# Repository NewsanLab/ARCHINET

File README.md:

# ARCHINET
Archi Net es una placa de desarrollo diseñada para facilitar la conectividad mediante WiFi, Ethernet y Bluetooth Low Energy (BLE). Cuenta con 4 entradas analógicas y 8 entradas/salidas digitales.

El diseño está pensado para que todas las funciones puedan ser programadas y controladas directamente desde el microcontrolador ARCHI (basado en RP2040), sin necesidad de programar el ESP32 por separado. Este actúa como un coprocesador de comunicaciones, operando mediante comandos enviados en formato Json.

## Especificaciones

* **Voltaje de Entrada del Shield:** 5V a 12V.
* **Conectividad Wi-Fi:** Estándar 802.11 b/g/n (2.4 GHz) con soporte para modos de estación, Punto de Acceso (AP) y Wi-Fi Direct (ESP32-S3).
* **Conectividad Bluetooth:** Bluetooth LE 5.0 (Bluetooth Low Energy).
* **Conectividad Ethernet:** Compatible con 10Base-T/100Base-TX Ethernet (WIZnet W5500).
* **Voltaje de Operación Interno:** Los módulos internos (ESP32-S3 y W5500) operan típicamente a 3.3V, provistos por reguladores a bordo del shield.
* **Pines de Entrada/Salida (I/O):**
    * 4 Entradas/Salidas Analógicas.
    * 8 Entradas/Salidas Digitales.
* **Programación/Depuración:** Incluye un puerto USB JTAG integrado para la programación y depuración directa del ESP32-S3.

## Diagrama en Bloques 

#### El shield ArchiNET se divide en 4 bloques funcionales principales:

* **Fuente de Alimentación:** Este bloque garantiza la alimentación estable a los bloques de conectividad.
* **Archi:** Es el microcontrolador principal que controla la comunicación y funcionalidad de los bloques de conectividad (ESP32 y Ethernet WIZNET W5500).
* **ESP32-S3:** Funciona como un coprocesador dedicado a la conectividad inalámbrica, comunicándose con Archi mediante interfaces como UART o SPI.
* **Ethernet (WIZNET W5500):** Proporciona la conexión de red cableada a través de un puerto RJ45, permitiendo una comunicación Ethernet.

## Fuente de alimentación
El siguiente diagrama en bloque muestra la distribución de voltaje.

El shield ArchiNet tiene una entrada para una fuente externa de +5V con una capacidad de hasta 2A.

Este voltaje de +5V se utiliza para la alimentación principal de la placa. La placa ArchiNet, a su vez, regula este voltaje para obtener una salida de +3.3V.

Esta salida de +3.3V es la que se utiliza para alimentar los módulos de bajo voltaje, como el Wiznet 5500 , el ESP32S3 y sensores

# 💻 Software

## Conexión a Ethernet

Para realizar una conexión por medio de Ethernet se deben tener cargadas las siguientes librerías en la carpeta `CIRCUITPY/lib`:

- `Adafruit_Bus_Device`
- `Adafruit_Wiznet5K`
- `Adafruit_Connection_Manager`
- `Adafruit_Requests`
- `Adafruit_Ticks`

### ⚙️ Configuración de pines

- **SPI**:
  - `SCK` → `GP10`
  - `MOSI` → `GP11`
  - `MISO` → `GP12`
  - `Chip Select (CS)` → `GP9`

###  Prueba de conexión inicial con ETHERNET

Este script permite comprobar que el dispositivo se conecta correctamente a la red mediante Ethernet.

### ¿Qué hace el script?

1. Configura el bus SPI y el pin CS.
2. Inicializa el módulo Ethernet `WIZNET5K`.
3. Crea una sesión HTTP con `adafruit_requests`.
4. Muestra:
   - Versión del chip
   - Dirección MAC
   - Dirección IP asignada

## Ejemplo: Consulta de IP por Ethernet

<a href="https://github.com/NewsanLab/ARCHINET/blob/main/Software/Example/Ethernet/Ejemplo%201%20Consulta%20IP/01.py" target="_blank" style="text-decoration:none; padding:6px 12px; background-color:#0366d6; color:white; border-radius:6px; font-weight:bold;"> Ver código completo en GitHub</a>

###  Fragmento del código 
```python
import board
import busio
import digitalio
import adafruit_connection_manager
import adafruit_requests
from adafruit_wiznet5k.adafruit_wiznet5k import WIZNET5K

spi = busio.SPI(board.GP10, MOSI=board.GP11, MISO=board.GP12)
cs = digitalio.DigitalInOut(board.GP9)
eth = WIZNET5K(spi, cs)

pool = adafruit_connection_manager.get_radio_socketpool(eth)
ssl_context = adafruit_connection_manager.get_radio_ssl_context(eth)
requests = adafruit_requests.Session(pool, ssl_context)

print("Chip Version:", eth.chip)
print("MAC Address:", [hex(i) for i in eth.mac_address])
print("My IP address is:", eth.pretty_ip(eth.ip_address))

```
## ESP32 como Coprocesador (modo UART)

El ESP32 se utiliza como coprocesador encargado de gestionar la conexión WiFi. La comunicación entre el microcontrolador principal (ej. RP2040, Archi u otros) y el ESP32 se realiza mediante UART o SPI, mediante el envío de **comandos en formato JSON**.

---

###  Modos de operación

- **UART**: Se comunica a través de pines TX/RX, usando comandos y respuestas JSON.
- **SPI**: Alternativamente, se puede implementar una versión basada en SPI (no cubierta en este ejemplo, pero compatible).

---

## Conexión WiFi / BLE vía UART

Este ejemplo muestra cómo controlar el ESP32 como coprocesador para conectarse a una red WiFi/BLE mediante UART.

### Conceptos clave

- Comunicación UART entre el microcontrolador principal y el ESP32.
- El pin `ready` indica cuándo el ESP32 está disponible para recibir comandos.
- Uso de JSON para enviar comandos como `CONNECT`, `SCAN`, `STATUS`, etc.
- Reset físico al ESP32 para asegurar un arranque limpio.

---

### ⚙️ Configuración de pines
- **UART y pines de control**:

  - `UART TX` → `GP12`
  - `UART RX` → `GP13`
  - `Pin ready` → `GP14`
  - `Pin reset` → `GP15`

---

### ¿Qué hace el script?

1. Reinicia el ESP32 con un pulso en el pin `reset`.
2. Espera la señal `ready` del ESP32.
3. Envía el comando `CONNECT` con SSID y contraseña.
4. Recibe las respuestas en formato JSON.
5. Finaliza cuando se recibe `{"end": true}` desde el ESP32.

---

###  Ejemplo: Primera conexión a la red

<a href="https://github.com/NewsanLab/ARCHINET/blob/main/Software/Example/WiFi/Conectar%20a%20WiFi/code.py" target="_blank" style="text-decoration:none; padding:6px 12px; background-color:#0366d6; color:white; border-radius:6px; font-weight:bold;"> Ver código completo en GitHub</a>

### Fragmento del código

```python
esp = ESP32UART(tx_pin=board.GP12, rx_pin=board.GP13, ready_pin=board.GP14)

if esp.esperar_ready(timeout=10):
    esp.solicitar_comando({"cmd": "CONNECT", "ssid": "tu_ssid", "pass": "tu_password"})
    esp.leer_respuesta(timeout=20)
else:
    print("ESP32 no está listo.")

```
---
### Ejemplo: Primera conexión mediante BLE 

Para iniciar comunicación BLE se realiza mediante la misma manera por comandos:

```python
 #Inicia BLE->Con el siguiente comando por defecto tiene el nombre de ARCHINET_BLEXX  
    print("\n--- TEST: CONNECT BLE---")
    esp.solicitar_comando({"cmd": "BLEINIT"})
    esp.leer_respuesta(timeout=20) #respuesta el nombre del dispositivo

    while True:
        esp.solicitar_comando({"cmd": "BLETX","data": "{pcb:archinet, version:v2}"})#tx
        esp.solicitar_comando({"cmd": "BLERX"})
        esp.leer_respuesta(timeout=15) #respuesta del ble rx
        time.sleep(2) 
```
Una vez que tienes la conexión hecha, puedes realizar  una app escritorio/celular para obtener datos. 

### Ejemplo de APP recepción y transmisión 

---

### 📋 Lista de comandos

| Comando       | Parámetros                      | Descripción                                                                 | 📄 Código de ejemplo                                                                 |
|---------------|----------------------------------|-----------------------------------------------------------------------------|--------------------------------------------------------------------------------------|
| `SCAN`        | *(ninguno)*                     | Escanea y lista redes WiFi disponibles.                                    | [🔗 Ver ejemplo](https://github.com/NewsanLab/ARCHINET/blob/main/Software/Example/WiFi/Escanear/code.py)          |
| `CONNECT`     | `ssid`, `pass`                  | Conecta a una red WiFi específica.                                         | [🔗 Ver ejemplo](https://github.com/NewsanLab/ARCHINET/blob/main/Software/Example/WiFi/Conectar%20a%20WiFi/code.py)       |
| `DISCONNECT`  | `target` (`"WiFi"` o `"AP"`)    | Desconecta de la red o cierra el punto de acceso.                          | [🔗 Ver ejemplo](https://github.com/NewsanLab/ARCHINET/blob/main/Software/Example/WiFi/Desconectar%20Red/code.py)    |
| `AP`          | `ssid`, `pass`                  | Crea un punto de acceso (Access Point).                                    | [🔗 Ver ejemplo](https://github.com/NewsanLab/ARCHINET/blob/main/Software/Example/WiFi/Conectar%20a%20AP/code.py)            |
| `PING`        | *(ninguno)*                     | Verifica si el ESP32 está activo y responde con su IP.                     | [🔗 Ver ejemplo](https://github.com/NewsanLab/ARCHINET/blob/main/Software/Example/WiFi/Informaci%C3%B3n%20de%20conexi%C3%B3n/code.py)          |
| `INFO`        | *(ninguno)*                     | Devuelve información del sistema: IP, RSSI y memoria disponible.           | [🔗 Ver ejemplo](https://github.com/NewsanLab/ARCHINET/blob/main/Software/Example/WiFi/Informaci%C3%B3n%20de%20conexi%C3%B3n/code.py)          |
| `GET`         | `url`                           | Realiza una petición HTTP GET a la URL indicada.                           | [🔗 Ver ejemplo](https://github.com/NewsanLab/ARCHINET/blob/main/Software/Example/WiFi/Consulta%20GET/code.py)           |
| `POST`        | `url`, `data`                   | Envía datos mediante HTTP POST (JSON) a la URL especificada.               | [🔗 Ver ejemplo](https://github.com/NewsanLab/ARCHINET/blob/main/Software/Example/WiFi/Consulta%20POST/code.py)          |
| `WebServer`   | `label`, `data`                 | Crea o actualiza un endpoint en el servidor embebido del ESP32.            | [🔗 Ver ejemplo](https://github.com/NewsanLab/ARCHINET/blob/main/Software/Example/WiFi/WebServer-API-WiFi/code.py)     |
| `HTML`        | `html`                          | Inyecta HTML personalizado en el servidor web embebido.                    | [🔗 Ver ejemplo](https://github.com/NewsanLab/ARCHINET/blob/main/Software/Example/WiFi/A%C3%B1adir%20HTML/codehtml.py)          |
| `UART_OFF`    | `UART_OFF`                      | Apaga el UART para utilizar el Ethernet, para volver utilzar reiniciar esp32.| [🔗 Ver ejemplo](https://github.com/NewsanLab/ARCHINET/blob/main/Software/Example/UART_OFF%26ETHERNET/Code.py) |
| `BLEINIT`    | *(ninguno o name)*                    | Inicia BLE por defecto crea el nombre del dispositivo | [🔗 Ver ejemplo](https://github.com/NewsanLab/ARCHINET/blob/main/Software/Example/BLE/code.py)|
| `BLETX`    |  `data`                   | Realiza la transmisión de datos de BLE , se debe mandar los datos en el parametro data en formato json | [🔗 Ver ejemplo](https://github.com/NewsanLab/ARCHINET/blob/main/Software/Example/BLE/code.py)|
| `BLERX`    |  *(ninguno)*                  | Realiza la recepción de datos de BLE  | [🔗 Ver ejemplo](https://github.com/NewsanLab/ARCHINET/blob/main/Software/Example/BLE/code.py)|
| `BLEOFF`    | *(ninguno o name)*                    | Desactiva el BLE | [🔗 Ver ejemplo](https://github.com/NewsanLab/ARCHINET/blob/main/Software/Example/BLE/BLEOFF.py)|

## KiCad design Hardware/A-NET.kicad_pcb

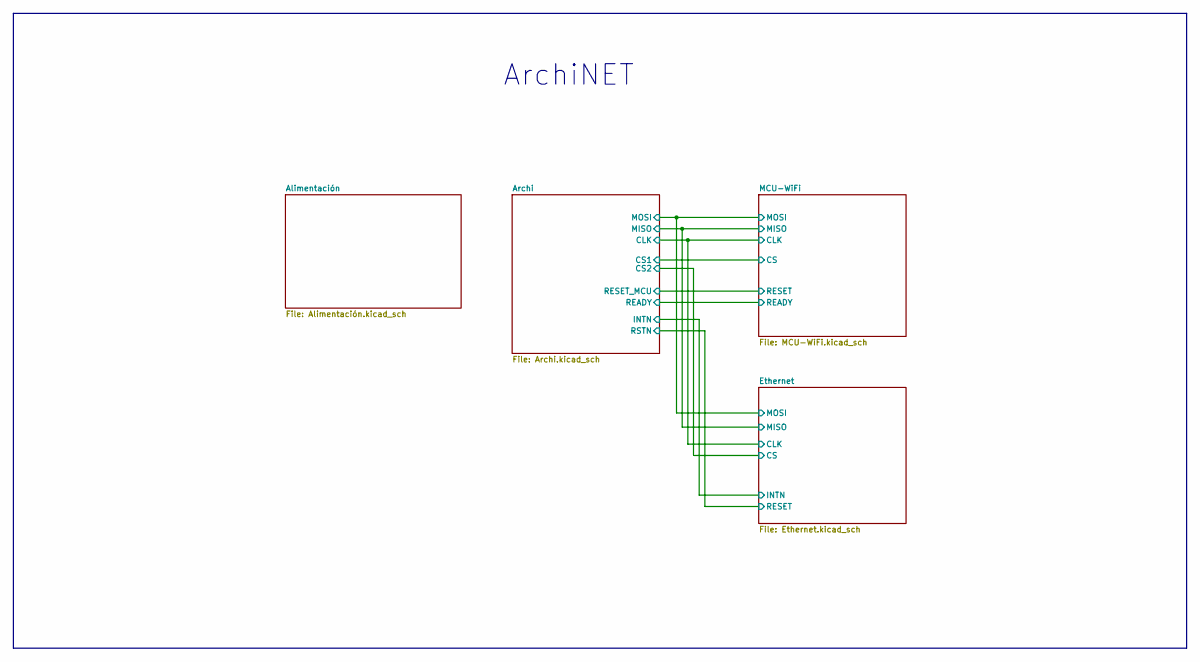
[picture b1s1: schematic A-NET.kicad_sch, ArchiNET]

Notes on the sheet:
ArchiNET

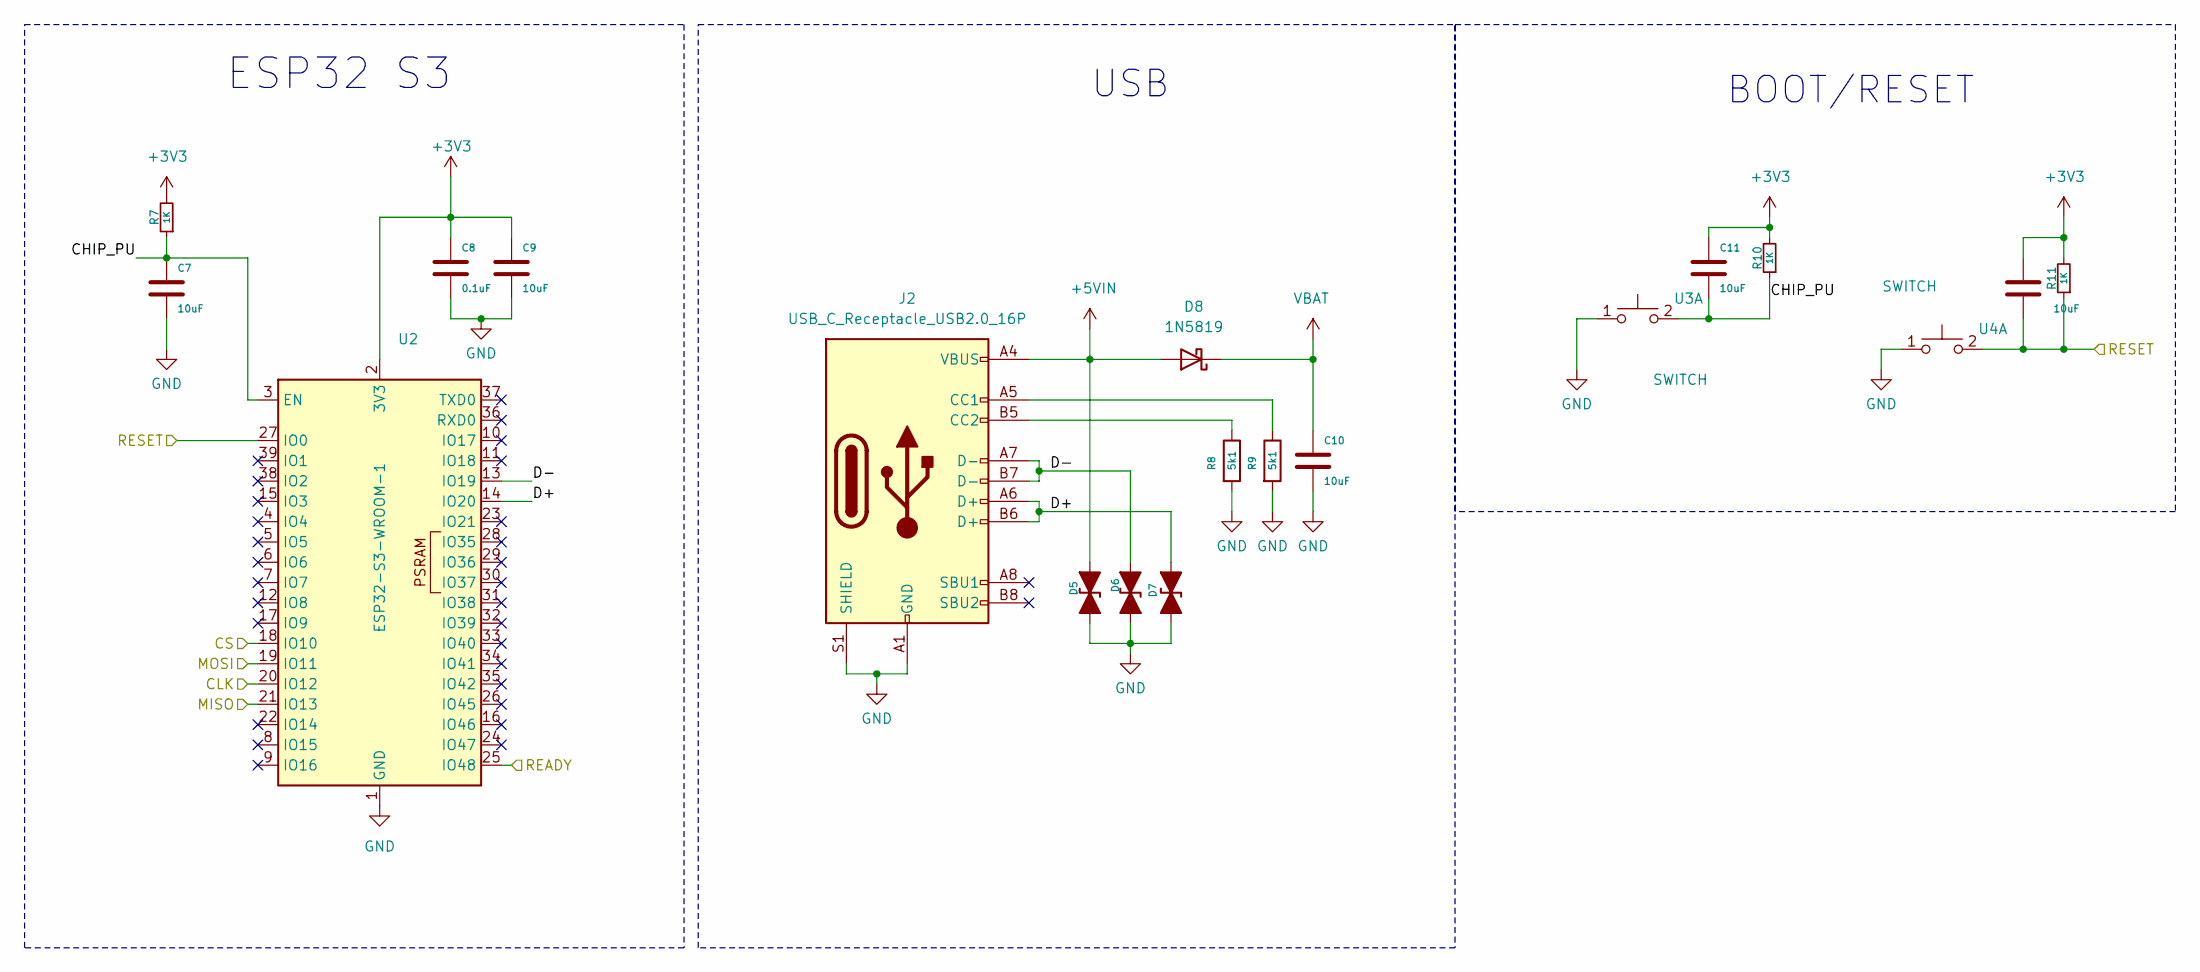
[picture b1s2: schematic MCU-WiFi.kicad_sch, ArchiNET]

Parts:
C7, C9, C10, C11, C12: 10uF; C_0603_1608Metric; PartNumber CL10X106MO8NRNC
C8: 0.1uF; C_0603_1608Metric; PartNumber CC0603KRX7R7BB104
D5, D6, D7: D_TVS_Filled; D_0402_1005Metric; PartNumber ESD9B5.0ST5G
D8: 1N5819; Nexperia_CFP3_SOD-123W; PartNumber 1N5819WS
J2: USB_C_Receptacle_USB2.0_16P; USB_C_Receptacle_HRO_TYPE-C-31-M-12; PartNumber USB4105-GF-A
R7, R10, R11: 1K; R_0603_1608Metric_Pad0.98x0.95mm_HandSolder; PartNumber RCS06031K00FKEA
R8, R9: 5k1; R_0402_1005Metric; PartNumber ERJ-PA2F5101X
U2: ESP32-S3-WROOM-1; PartNumber ESP32-S3-WROOM-1-N8
U3, U4: SWITCH; SW_Push_1P1T_XKB_TS-1187A; PartNumber PTS526SK15SMTR2 LFS

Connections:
+3V3: C8.1, C9.1, C11.1, C12.1, R7.2, R10.2, R11.2, U2.2 (3V3); also elsewhere on the board
+5VIN: D5.2 (A2), D8.2 (A), J2.A4 (VBUS), J2.A9 (VBUS), J2.B4 (VBUS), J2.B9 (VBUS); also elsewhere on the board
/Archi/CLK: U2.20 (IO12); also elsewhere on the board
/Archi/CS1: U2.18 (IO10); also elsewhere on the board
/Archi/MISO: U2.21 (IO13); also elsewhere on the board
/Archi/MOSI: U2.19 (IO11); also elsewhere on the board
/Archi/READY: U2.25 (IO48); also elsewhere on the board
/Archi/RESET_MCU: C12.2, R11.1, U2.27 (IO0), U4.2 (D); also elsewhere on the board
/MCU-WiFi/CHIP_PU: C7.1, C11.2, R7.1, R10.1, U2.3 (EN), U3.2 (D)
/MCU-WiFi/D+: D7.2 (A2), J2.A6 (D+), J2.B6 (D+), U2.14 (IO20)
/MCU-WiFi/D-: D6.2 (A2), J2.A7 (D-), J2.B7 (D-), U2.13 (IO19)
GND: C7.2, C8.2, C9.2, C10.2, D5.1 (A1), D6.1 (A1), D7.1 (A1), J2.A1 (GND), J2.A12 (GND), J2.B1 (GND), J2.B12 (GND), J2.S1 (SHIELD), R8.2, R9.2, U2.1 (GND), U2.40 (GND), U2.41 (GND), U3.1 (C), U4.1 (C); also elsewhere on the board
unnamed: J2.A5 (CC1), R9.1
unnamed: J2.B5 (CC2), R8.1
VBAT: C10.1, D8.1 (K); also elsewhere on the board

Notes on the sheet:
USB
BOOT/RESET
ESP32 S3

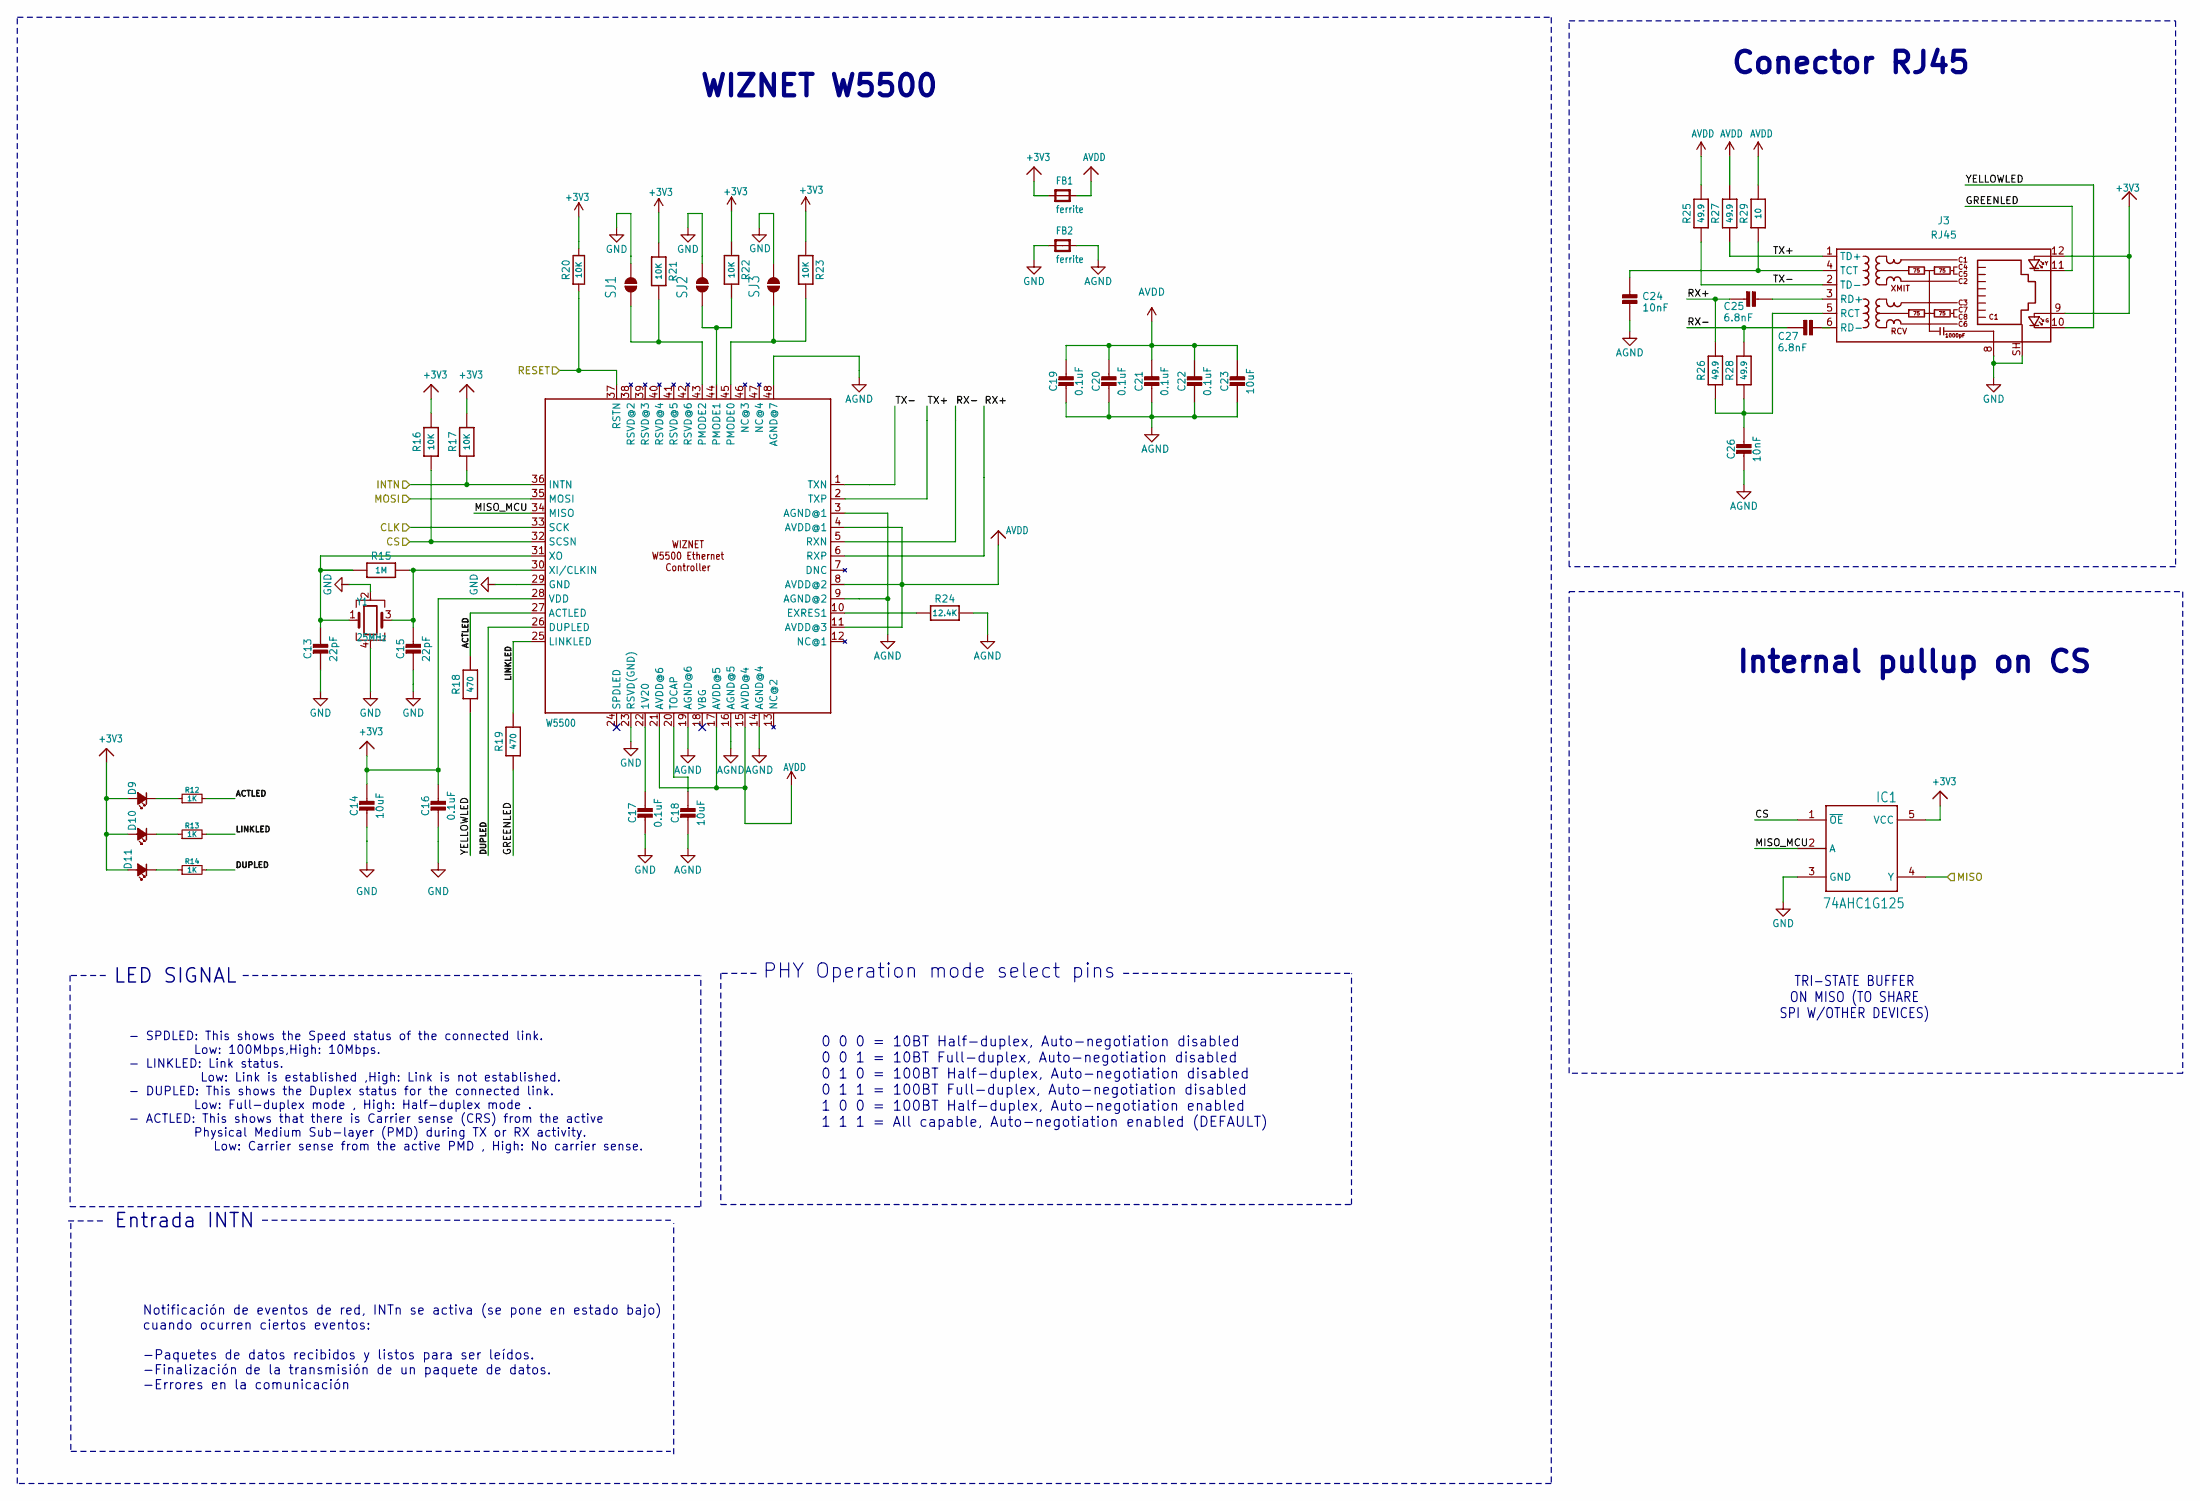
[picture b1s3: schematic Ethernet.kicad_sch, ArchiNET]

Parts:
C13, C15: 22pF; C_0603_1608Metric; PartNumber C0603C220K4GACTU
C14, C18, C23: 10uF; C_0603_1608Metric; PartNumber CL10X106MO8NRNC
C16, C17, C19, C20, C21, C22: 0.1uF; C_0603_1608Metric; PartNumber CC0603KRX7R7BB104
C24, C26: 10nF; C_0603_1608Metric; PartNumber C0603C103K4RECTU
C25, C27: 6.8nF; C_0603_1608Metric; PartNumber KGM15AR71C682KT
D9, D10, D11: LED_POW; LED_0603_1608Metric_Pad1.05x0.95mm_HandSolder; PartNumber B1931NG--20D001114U1930
FB1: ferrite; L_0603_1608Metric; PartNumber MH1608-121Y
FB2: ferrite; R_0603_1608Metric; PartNumber MH1608-121Y
IC1: 74AHC1G125; SOT-353_SC-70-5; PartNumber SN74AHC1G125DCKR
J3: RJ45; CONN12_ARJM11B1-009-AB-EW2_ABR; PartNumber ARJM11B1-009-AB-EW2
R12, R13, R14: 1K; R_0603_1608Metric_Pad0.98x0.95mm_HandSolder; PartNumber RCS06031K00FKEA
R15: 1M; R_0603_1608Metric; PartNumber RCS06031M00FKEA
R16, R17, R20, R21, R22, R23: 10K; R_0603_1608Metric; PartNumber RCS060310K0JNEA
R18, R19: 470; R_0603_1608Metric; PartNumber CRGP0603F470R
R24: 12.4K; R_0603_1608Metric; PartNumber RCS060312K4FKEA
R25, R26, R27, R28: 49.9; R_0603_1608Metric; PartNumber RCS060349R9FKEA
R29: 10; R_0603_1608Metric; PartNumber RCS060310R0FKEA
SJ1, SJ2, SJ3: SOLDERJUMPERREFLOW_NOPASTE; Jumper
U$1: W5500; PartNumber W5500
Y1: 25MHz; Crystal_SMD_TXC_7M-4Pin_3.2x2.5mm; PartNumber ABM3B-25.000MHZ-22-E-4-H-T

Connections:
+3V3: C14.1, C16.1, D9.2 (A), D10.2 (A), D11.2 (A), FB1.1, IC1.5 (VCC), J3.9, J3.12, R16.2, R17.2, R20.1, R21.1, R22.1, R23.1, U$1.28 (VDD); also elsewhere on the board
/Archi/CLK: U$1.33 (SCK); also elsewhere on the board
/Archi/INTN: R17.1, U$1.36 (INTN); also elsewhere on the board
/Archi/MISO: IC1.4 (Y); also elsewhere on the board
/Archi/MOSI: U$1.35 (MOSI); also elsewhere on the board
/Archi/RSTN: R20.2, U$1.37 (RSTN); also elsewhere on the board
/Ethernet/ACTLED: R12.2, R18.2, U$1.27 (ACTLED)
/Ethernet/CS: IC1.1 (~OE), R16.1, U$1.32 (SCSN); also elsewhere on the board
/Ethernet/DUPLED: R14.2, U$1.26 (DUPLED)
/Ethernet/GREENLED: J3.11, R19.1
/Ethernet/LINKLED: R13.2, R19.2, U$1.25 (LINKLED)
/Ethernet/MISO_MCU: IC1.2 (A), U$1.34 (MISO)
/Ethernet/RX+: C25.2, R26.2, U$1.6 (RXP)
/Ethernet/RX-: C27.2, R28.2, U$1.5 (RXN)
/Ethernet/TX+: J3.1 (TD+), R27.1, U$1.2 (TXP)
/Ethernet/TX-: J3.2 (TD-), R25.1, U$1.1 (TXN)
/Ethernet/YELLOWLED: J3.10, R18.1
AGND: C18.2, C19.2, C20.2, C21.2, C22.2, C23.2, C24.2, C26.2, FB2.2, R24.2, U$1.3 (AGND@1), U$1.9 (AGND@2), U$1.14 (AGND@4), U$1.16 (AGND@5), U$1.19 (AGND@6), U$1.48 (AGND@7)
AVDD: C19.1, C20.1, C21.1, C22.1, C23.1, FB1.2, R25.2, R27.2, R29.2, U$1.4 (AVDD@1), U$1.8 (AVDD@2), U$1.11 (AVDD@3), U$1.15 (AVDD@4), U$1.17 (AVDD@5), U$1.21 (AVDD@6)
GND: C13.2, C14.2, C15.2, C16.2, C17.2, FB2.1, IC1.3 (GND), J3.8, J3.SH, SJ1.2 (B), SJ2.2 (B), SJ3.2 (B), U$1.23 (RSVD(GND)), U$1.29 (GND), Y1.2, Y1.4; also elsewhere on the board
unnamed: D9.1 (K), R12.1
unnamed: D10.1 (K), R13.1
unnamed: D11.1 (K), R14.1
unnamed: C26.1, J3.5 (RCT), R26.1, R28.1
unnamed: C25.1, J3.3 (RD+)
unnamed: C27.1, J3.6 (RD-)
unnamed: C24.1, J3.4 (TCT), R29.1
unnamed: R21.2, SJ1.1 (A), U$1.43 (PMODE2)
unnamed: R22.2, SJ2.1 (A), U$1.44 (PMODE1)
unnamed: R23.2, SJ3.1 (A), U$1.45 (PMODE0)
unnamed: C17.1, U$1.22 (1V20)
unnamed: R24.1, U$1.10 (EXRES1)
unnamed: C18.1, U$1.20 (TOCAP)
unnamed: C15.1, R15.2, U$1.30 (XI/CLKIN), Y1.3
unnamed: C13.1, R15.1, U$1.31 (XO), Y1.1

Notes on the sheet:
PHY Operation mode select pins
Internal pullup on CS
Notificación de eventos de red, INTn se activa (se pone en estado bajo) cuando ocurren ciertos eventos: -Paquetes de datos recibidos y listos para ser leídos. -Finalización de la transmisión de un paquete de datos. -Errores en la comunicación
LED SIGNAL
TRI-STATE BUFFER ON MISO (TO SHARE SPI W/OTHER DEVICES)
0 0 0 = 10BT Half-duplex, Auto-negotiation disabled 0 0 1 = 10BT Full-duplex, Auto-negotiation disabled 0 1 0 = 100BT Half-duplex, Auto-negotiation disabled 0 1 1 = 100BT Full-duplex, Auto-negotiation disabled 1 0 0 = 100BT Half-duplex, Auto-negotiation enabled 1 1 1 = All capable, Auto-negotiation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
WIZNET W5500
- SPDLED: This shows the Speed status of the connected link. Low: 100Mbps,High: 10Mbps. - LINKLED: Link status. Low: Link is established ,High: Link is not established. - DUPLED: This shows the Duplex status for the connected link. Low: Full-duplex mode , High: Half-duplex mode . - ACTLED: This sho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
Entrada INTN
Conector RJ45

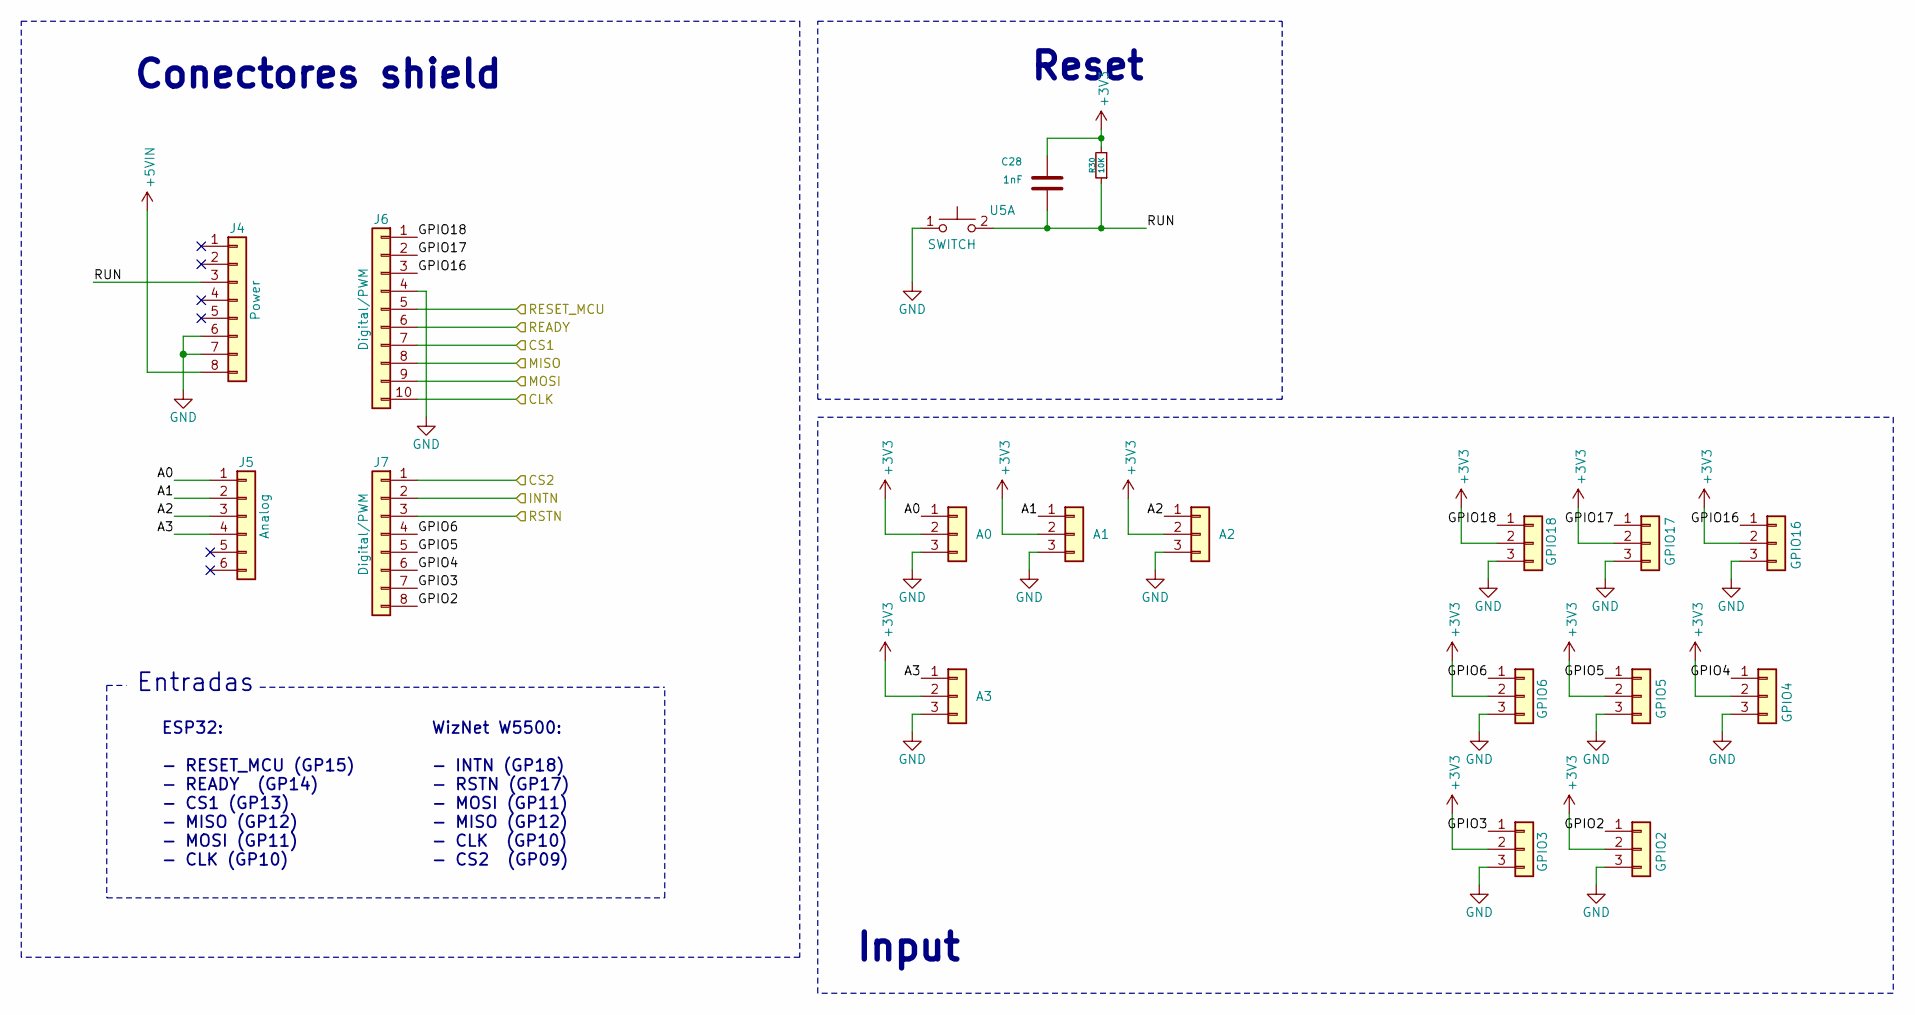
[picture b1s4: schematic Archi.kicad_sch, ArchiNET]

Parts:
A0, A1, A2, A3: Conn_01x03; PinHeader_1x03_P2.54mm_Vertical
C28: 1nF; C_0603_1608Metric_Pad1.08x0.95mm_HandSolder; PartNumber GRM1885C1H102JA01D
GPIO2, GPIO3, GPIO4, GPIO5, GPIO6, GPIO16, GPIO17, GPIO18: Conn_01x03; PinHeader_1x03_P2.54mm_Vertical
J4: Power; PinHeader_1x08_P2.54mm_Vertical
J5: Analog; PinHeader_1x06_P2.54mm_Vertical
J6: Digital/PWM; PinHeader_1x10_P2.54mm_Vertical
J7: Digital/PWM; PinHeader_1x08_P2.54mm_Vertical
R30: 10K; R_0603_1608Metric_Pad0.98x0.95mm_HandSolder; PartNumber RCS060310K0JNEA
U5: SWITCH; SW_Push_1P1T_XKB_TS-1187A; PartNumber PTS526SK15SMTR2 LFS

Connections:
+3V3: A0.2, A1.2, A2.2, A3.2, C28.1, GPIO2.2, GPIO3.2, GPIO4.2, GPIO5.2, GPIO6.2, GPIO16.2, GPIO17.2, GPIO18.2, R30.2; also elsewhere on the board
+5VIN: J4.8; also elsewhere on the board
/Archi/A0: A0.1, J5.1
/Archi/A1: A1.1, J5.2
/Archi/A2: A2.1, J5.3
/Archi/A3: A3.1, J5.4
/Archi/CLK: J6.10; also elsewhere on the board
/Archi/CS1: J6.7; also elsewhere on the board
/Archi/GPIO2: GPIO2.1, J7.8
/Archi/GPIO3: GPIO3.1, J7.7
/Archi/GPIO4: GPIO4.1, J7.6
/Archi/GPIO5: GPIO5.1, J7.5
/Archi/GPIO6: GPIO6.1, J7.4
/Archi/GPIO16: GPIO16.1, J6.3
/Archi/GPIO17: GPIO17.1, J6.2
/Archi/GPIO18: GPIO18.1, J6.1
/Archi/INTN: J7.2; also elsewhere on the board
/Archi/MISO: J6.8; also elsewhere on the board
/Archi/MOSI: J6.9; also elsewhere on the board
/Archi/READY: J6.6; also elsewhere on the board
/Archi/RESET_MCU: J6.5; also elsewhere on the board
/Archi/RSTN: J7.3; also elsewhere on the board
/Archi/RUN: C28.2, J4.3, R30.1, U5.2 (D)
/Ethernet/CS: J7.1; also elsewhere on the board
GND: A0.3, A1.3, A2.3, A3.3, GPIO2.3, GPIO3.3, GPIO4.3, GPIO5.3, GPIO6.3, GPIO16.3, GPIO17.3, GPIO18.3, J4.6, J4.7, J6.4, U5.1 (C); also elsewhere on the board

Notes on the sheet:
WizNet W5500: - INTN (GP18) - RSTN (GP17) - MOSI (GP11) - MISO (GP12) - CLK (GP10) - CS2 (GP09)
Reset
ESP32: - RESET_MCU (GP15) - READY (GP14) - CS1 (GP13) - MISO (GP12) - MOSI (GP11) - CLK (GP10)
Input
Entradas
Conectores shield

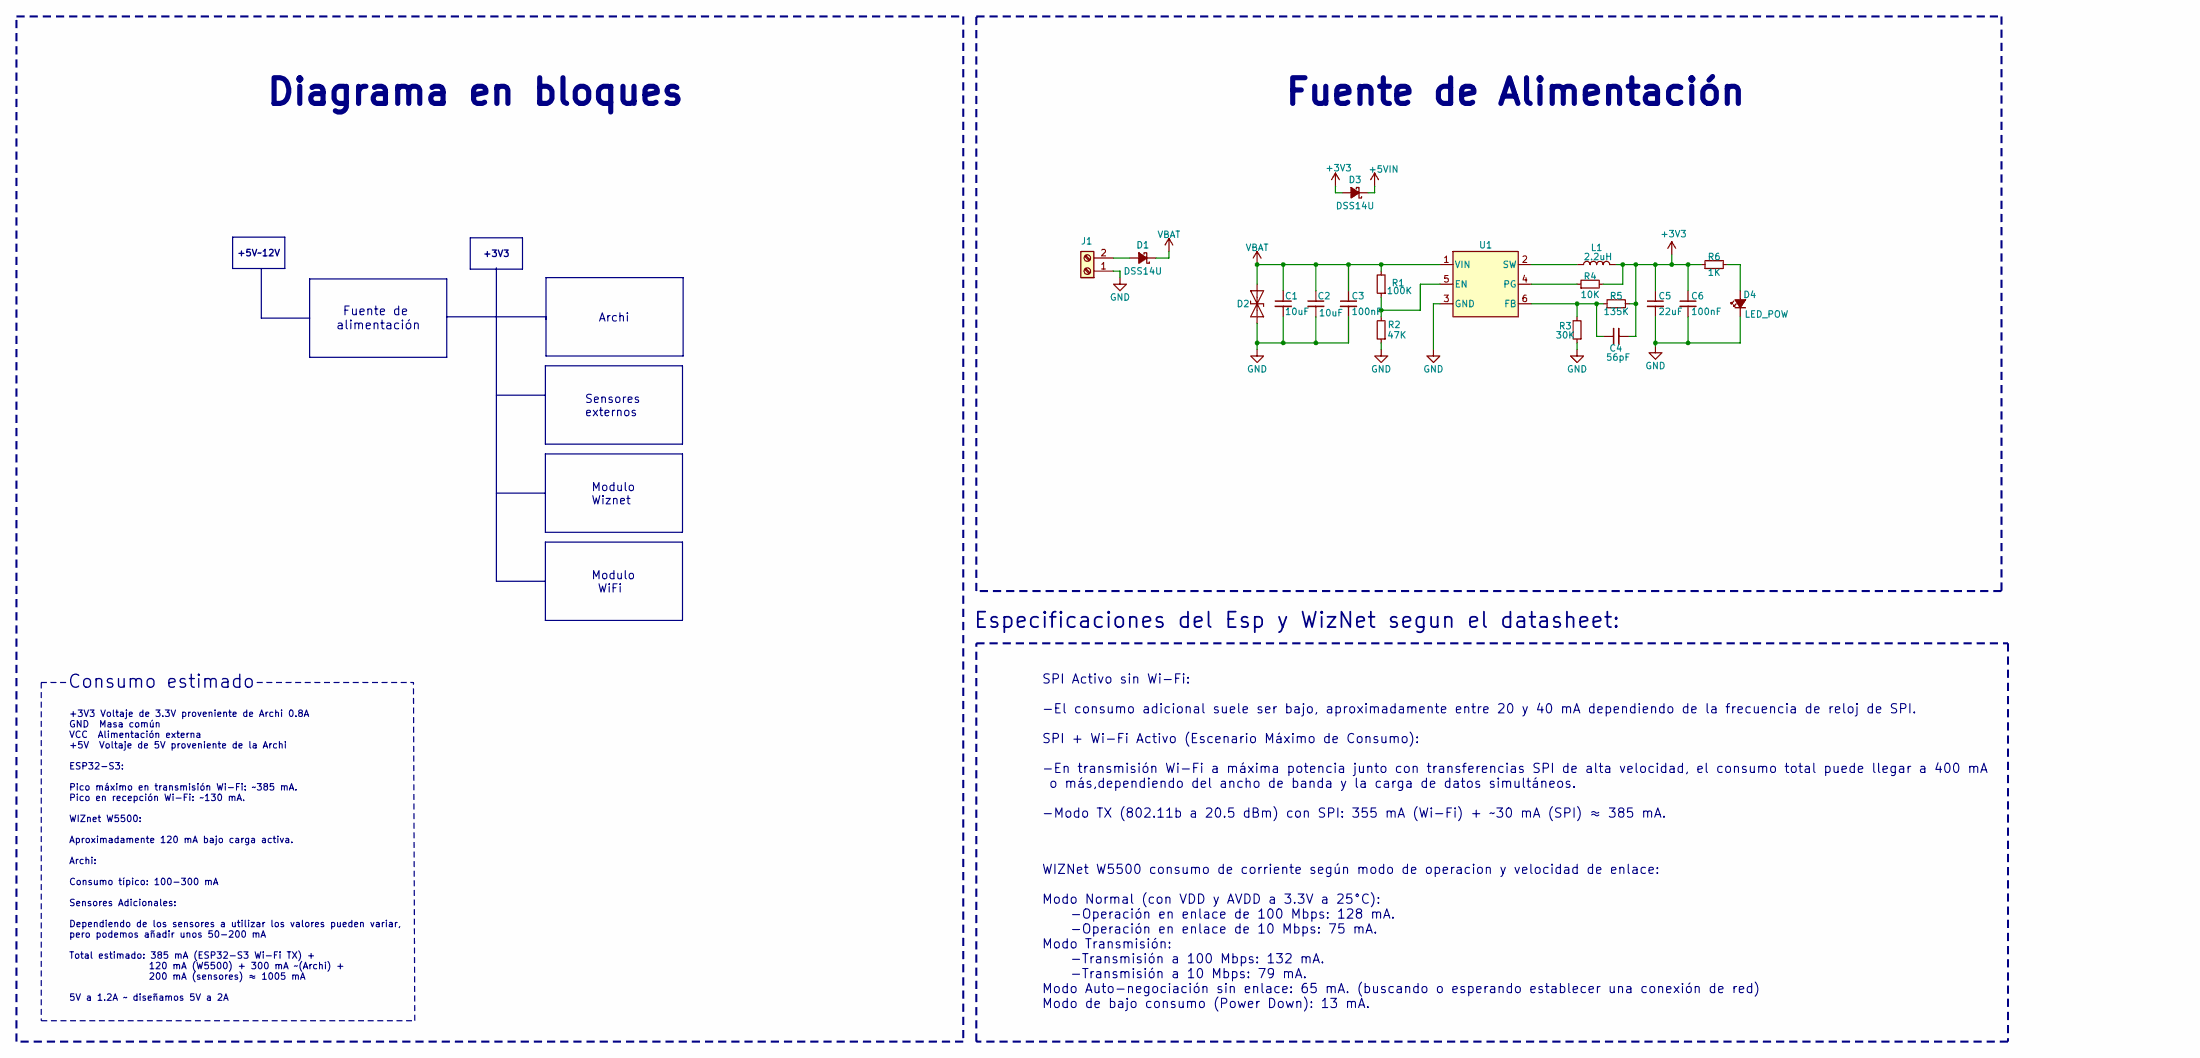
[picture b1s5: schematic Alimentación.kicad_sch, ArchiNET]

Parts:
C1, C2: 10uF; C_0603_1608Metric; PartNumber CL10X106MO8NRNC
C3, C6: 100nF; C_0603_1608Metric; PartNumber CC0603KRX7R7BB104
C4: 56pF; C_0603_1608Metric; PartNumber C0603C560M3HACTU
C5: 22uF; C_0603_1608Metric; PartNumber GRM188R61A226ME15D
D1, D3: DSS14U; D_SOD-123F; PartNumber DSS14U
D2: SD12C-7; D_SOD-323_HandSoldering; PartNumber SD12C-7
D4: LED_POW; LED_0603_1608Metric; PartNumber B1931NG--20D001114U1930
J1: BAT; TerminalBlock_RND_205-00287_1x02_P5.08mm_Horizontal; PartNumber VI0221520000G
L1: 2.2uH; IND_PA4332.222NLT; PartNumber PA4332.222NLT
R1: 100K; R_0603_1608Metric; PartNumber SR0603FR-7T100KL
R2: 47K; R_0603_1608Metric; PartNumber RCS060332K4FKEA
R3: 30K; R_0603_1608Metric; PartNumber RCS060310K0JNEA
R4: 10K; R_0603_1608Metric; PartNumber RCS060310K0JNEA
R5: 135K; R_0603_1608Metric; PartNumber RT0603BRD07135KL
R6: 1K; R_0603_1608Metric; PartNumber RCS06031K00FKEA
U1: TPS563252DRLR; SOT6_DRL_TEX-L; PartNumber TPS563252DRLR

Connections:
+3V3: C4.2, C5.1, C6.1, D3.2 (A), L1.2, R4.2, R5.2, R6.1; also elsewhere on the board
+5VIN: D3.1 (K); also elsewhere on the board
GND: C1.2, C2.2, C3.2, C5.2, C6.2, D2.2 (A2), D4.1 (K), J1.1, R2.1, R3.1, U1.3 (GND); also elsewhere on the board
unnamed: D1.2 (A), J1.2
unnamed: D4.2 (A), R6.2
unnamed: R1.1, R2.2, U1.5 (EN)
unnamed: C4.1, R3.2, R5.1, U1.6 (FB)
unnamed: R4.1, U1.4 (PG)
unnamed: L1.1, U1.2 (SW)
VBAT: C1.1, C2.1, C3.1, D1.1 (K), D2.1 (A1), R1.2, U1.1 (VIN); also elsewhere on the board

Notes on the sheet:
Modulo Wiznet
SPI Activo sin Wi-Fi: -El consumo adicional suele ser bajo, aproximadamente entre 20 y 40 mA dependiendo de la frecuencia de reloj de SPI. SPI + Wi-Fi Activo (Escenario Máximo de Consumo): -En transmisión Wi-Fi a máxima potencia junto con transferencias SPI de alta velocidad, el consumo total puede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
Consumo estimado
Diagrama en bloques
WIZNet W5500 consumo de corriente según modo de operacion y velocidad de enlace: Modo Normal (con VDD y AVDD a 3.3V a 25°C): -Operación en enlace de 100 Mbps: 128 mA. -Operación en enlace de 10 Mbps: 75 mA. Modo Transmisión: -Transmisión a 100 Mbps: 132 mA. -Transmisión a 10 Mbps: 79 mA. Modo Auto-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
+5V~12V
+3V3
Especificaciones del Esp y WizNet segun el datasheet:
Sensores externos
Archi
Modulo WiFi
Fuente de Alimentación
Fuente de alimentación
+3V3 Voltaje de 3.3V proveniente de Archi 0.8A GND Masa común VCC Alimentación externa +5V Voltaje de 5V proveniente de la Archi ESP32-S3: Pico máximo en transmisión Wi-Fi: ~385 mA. Pico en recepción Wi-Fi: ~130 mA. WIZnet W5500: Aproximadamente 120 mA bajo carga activa. Archi: Consumo típico: 100-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

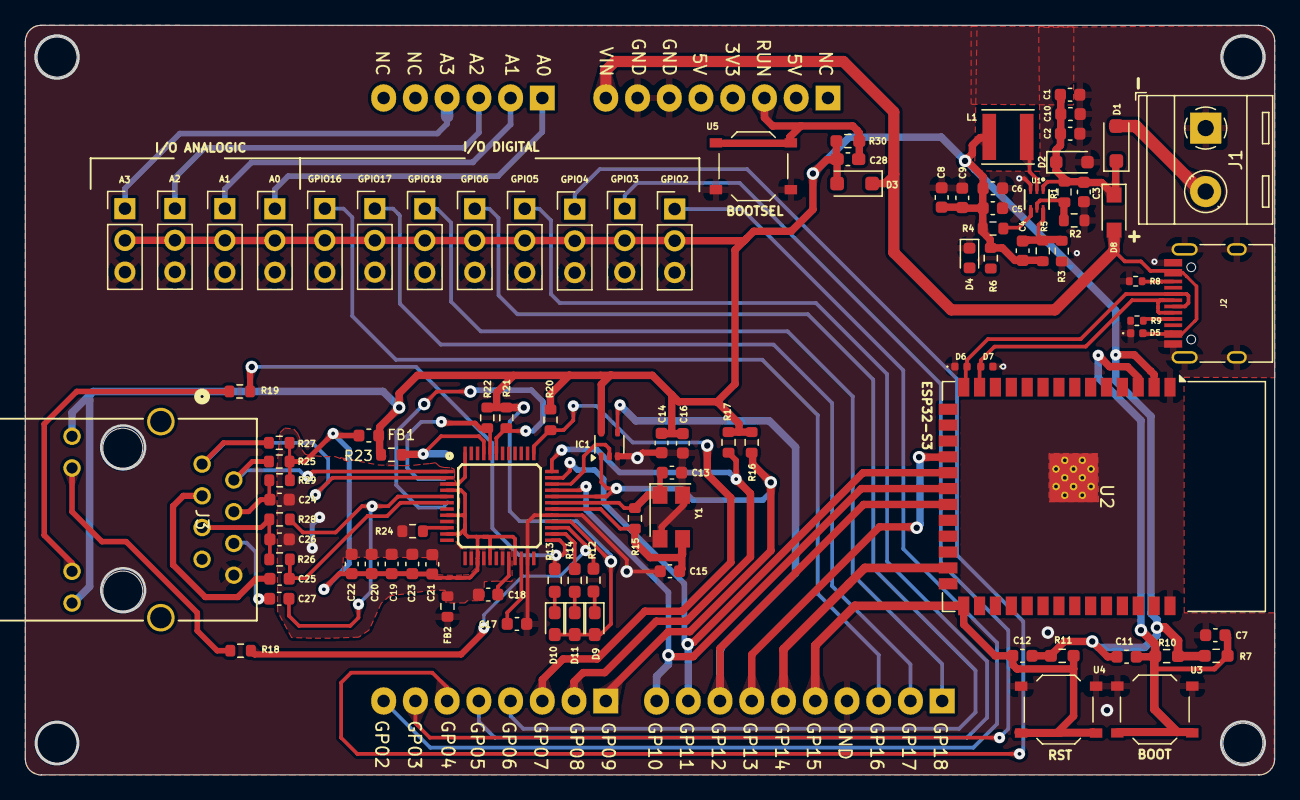
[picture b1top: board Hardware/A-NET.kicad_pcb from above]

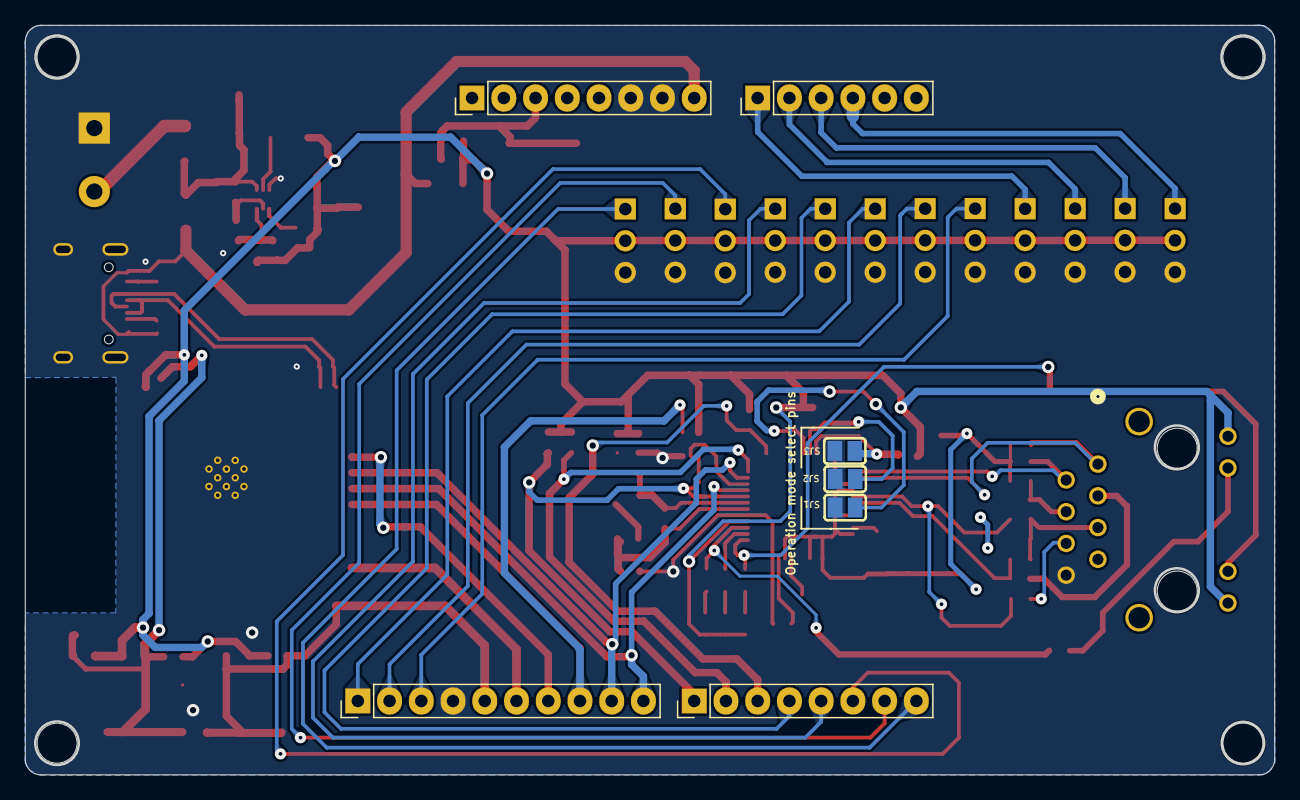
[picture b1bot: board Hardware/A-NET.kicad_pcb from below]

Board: 2 copper layers, 99.8 x 59.8 mm, 106 parts (4 on the bottom side), 64 nets.

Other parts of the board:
MH1, MH2, MH3, MH4: MountingHole_3.2mm
